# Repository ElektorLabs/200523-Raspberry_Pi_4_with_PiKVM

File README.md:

#  200523 - Raspberry Pi4 with PiKVM

This contains PCBs tools and tips for PiKVM on the Raspberry Pi 4

## Getting Started

Have a look at the article on Elektor and on the PiKVM GitHub page https://github.com/pikvm/pikvm

## Hardware
 * [USB Data and Power Splitter](https://github.com/ElektorLabs/200523-Raspberry_Pi_4_with_PiKVM/tree/main/USB%20Power%20Splitter)

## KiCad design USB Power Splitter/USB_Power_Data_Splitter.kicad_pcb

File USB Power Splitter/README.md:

#  200523 - USB Data and Power Splitter

This contains PCBs to be used with PiKVM on the Raspberry Pi 4

## Created using KiCad

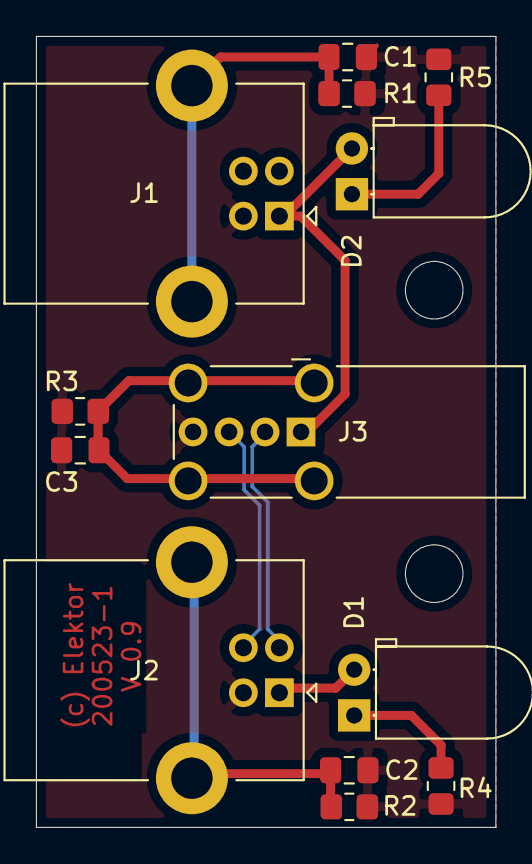
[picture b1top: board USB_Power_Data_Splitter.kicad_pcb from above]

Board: 2 copper layers, 25.5 x 43.9 mm, 15 parts (0 on the bottom side), 10 nets.

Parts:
C1, C2, C3: 100nF; C_0805_2012Metric_Pad1.18x1.45mm_HandSolder
D1, D2: LED RED; LED_D5.0mm_Horizontal_O1.27mm_Z3.0mm
H1, H2: MountingHole; MountingHole_3.2mm_M3
J1, J2: USB_B; USB_B_Lumberg_2411_02_Horizontal
J3: USB_A; USB_A_Wuerth_614004134726_Horizontal
R1, R2, R3: 100k; R_0805_2012Metric_Pad1.20x1.40mm_HandSolder
R4: 1K; R_0805_2012Metric_Pad1.20x1.40mm_HandSolder
R5: 1k; R_0805_2012Metric_Pad1.20x1.40mm_HandSolder

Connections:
D+: J2.3, J3.3
D-: J2.2, J3.2
GND: C1.1, C2.1, C3.1, J1.4, J2.4, J3.4, R1.2, R2.2, R3.2, R4.2, R5.2
unnamed: C1.2, J1.5, R1.1
unnamed: C2.2, J2.5, R2.1
unnamed: C3.2, J3.5, R3.1
unnamed: D1.1, R4.1
unnamed: D1.2, J2.1
unnamed: D2.1, R5.1
unnamed: D2.2, J1.1, J3.1

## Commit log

2021-05-04 Updated and added Readme
2021-07-01 Added BOM
    iBOM and BOM added
